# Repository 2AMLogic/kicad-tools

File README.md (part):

# kicad-tools

**Tools for AI agents to work with KiCad projects.**

🌐 **Live demo gallery: [kicad-tools.org](https://kicad-tools.org)** — explore example boards built end-to-end by these tools, with 2D/3D renders, routing & manufacturing metrics, downloadable fabrication packages, and an interactive in-browser PCB viewer.

This project provides standalone Python tools that enable AI agents (LLMs, autonomous coding assistants, etc.) to parse, analyze, and manipulate KiCad schematic and PCB files programmatically. All tools output machine-readable JSON and require no running KiCad instance.

**Preparing a board for JLCPCB assembly?** Check the layout against JLCPCB rules, look up LCSC parts, and export Gerbers, a bill of materials and component placements. With a signed-off bundle, `kct submit-jlcpcb --dry-run` checks stock for your board quantity and writes a local submission plan and review page. [JLCPCB assembly walkthrough](docs/guides/submission-preparation.md)

## Why Agent-Focused?

Traditional EDA tools require GUIs and manual interaction. `kicad-tools` bridges the gap by providing:

- **Structured data access** - Parse KiCad files into clean Python objects
- **Machine-readable output** - Analysis and query commands offer JSON output; check each command’s `--help` for supported formats
- **Programmatic modification** - Edit schematics and PCBs without a GUI
- **LLM reasoning interface** - Purpose-built module for LLM-driven PCB layout decisions

Whether you're building an AI assistant that reviews PCB designs, automating DRC checks in CI, or experimenting with LLM-driven routing, these tools provide the foundation.

## Installation

```bash
# Base install (CPU only)
pip install kicad-tools

# With CUDA GPU acceleration (NVIDIA GPUs on Linux/Windows)
pip install kicad-tools[cuda]

# With Metal GPU acceleration (Apple Silicon Macs)
pip install kicad-tools[metal]

# With native C++ router backend
pip install kicad-tools[native]

# With CMA-ES placement optimization (kct optimize-placement / kct build --optimize-placement)
pip install kicad-tools[placement]

# Everything (all optional dependencies)
pip install kicad-tools[all]
```

> The `placement` extra pulls in `cmaes` (and, transitively, `scipy`). It is
> required by `kct optimize-placement` and the placement step of
> `kct build --optimize-placement`; without it those commands exit with a
> clear message naming the extra. The `dev` and `all` extras already include
> it, so `uv sync --extra dev` is sufficient for development.

To check GPU acceleration status:
```bash
kct calibrate --show-gpu
```

### In a board (consumer) repository

The supported setup for a PCB-design repo that depends on kicad-tools is **PyPI
plus a committed `uv.lock`**: `pyproject.toml` carries a lower bound
(`kicad-tools[<extras>]>=X`) and `uv.lock` is the exact pin. Install it, with
the agent skills, CI gates and conventions, from a kicad-tools checkout:

```bash
./scripts/install-kct.sh /path/to/board-repo        # PyPI floor (default; same as --pypi)
./scripts/install-kct.sh --upgrade-workflow /path/to/board-repo  # + weekly upgrade PR
cd /path/to/board-repo && uv lock && uv sync && uv run kct build-native
```

The installer keeps the repo's existing extras and removes any
`[tool.uv.sources]` kicad-tools entry. Re-running it is a no-op when the floor
is already current. `--upgrade-workflow` adds `.github/workflows/kct-upgrade.yml`,
which opens a PR for each new PyPI release; the PR raises the floor, refreshes
`uv.lock` and the vendored files, and lists the release's upgrade notes.
`kct doctor` checks that the vendored files match the installed version.

Git and SHA pins (`--tag vX.Y.Z`, `--rev <sha>`) and local checkouts
(`--path ../kicad-tools`) are escape hatches for short-lived use. If you need
a fix that is not on PyPI yet, ask for a patch release rather than carrying a
SHA pin. Run `./scripts/install-kct.sh --help` for every option.

## Quick Start

### Command Line (`kct`)

```bash
# List symbols in a schematic
kct symbols project.kicad_sch
kct symbols project.kicad_sch --format json

# Trace nets
kct nets project.kicad_sch
kct nets project.kicad_sch --net VCC

# Generate bill of materials
kct bom project.kicad_sch
kct bom project.kicad_sch --format csv --group

# Run ERC (requires kicad-cli)
kct erc project.kicad_sch
kct erc project.kicad_sch --errors-only

# Run DRC with manufacturer rules
kct drc board.kicad_pcb
kct drc board.kicad_pcb --mfr jlcpcb
kct mfr compare  # Compare manufacturer rules
```

### Python API

```python
from kicad_tools import load_schematic, Schematic

# Load and parse a schematic
doc = load_schematic("project.kicad_sch")
sch = Schematic(doc)

# Access symbols
for symbol in sch.symbols:
    print(f"{symbol.reference}: {symbol.value}")

# Access hierarchy
for sheet in sch.sheets:
    print(f"Sheet: {sheet.name}")
```

### PCB Autorouter

```python
from kicad_tools.router import Autorouter, DesignRules

# Configure design rules
rules = DesignRules(
    grid_resolution=0.25,  # mm
    trace_width=0.2,  # mm
    trace_clearance=0.15,  # mm
)

# Create router and add components
router = Autorouter(width=100, height=80, rules=rules)
router.add_component("U1", pads=[{"number": "1", "x": 10, "y": 10, "net": 1}])
router.add_component("U2", pads=[{"number": "1", "x": 20, "y": 10, "net": 1}])

# Route all nets
routes = router.route_all(timeout=30)
print(f"Created {len(routes)} routes")
```

### LLM-Driven PCB Layout

The reasoning module enables LLMs to make strategic PCB layout decisions while tools handle geometric execution:

```python
from kicad_tools import PCBReasoningAgent

# Load board
agent = PCBReasoningAgent.from_pcb("board.kicad_pcb")

# Reasoning loop
while not agent.is_complete():
    # Get state as prompt for LLM
    prompt = agent.get_prompt()

    # Call your LLM (OpenAI, Anthropic, local, etc.)
    command = call_llm(prompt)

    # Execute and get feedback
    result, diagnosis = agent.execute(command)

# Save result
agent.save("board_routed.kicad_pcb")
```

CLI usage:
```bash
# Export state for external LLM
kct reason board.kicad_pcb --export-state

# Interactive mode
kct reason board.kicad_pcb --interactive

# Auto-route priority nets
kct reason board.kicad_pcb --auto-route
```

See `examples/llm-routing/` for complete examples.

### MCP Server for AI Agents

Enable AI assistants like Claude to interact with KiCad designs via the Model Context Protocol:

```bash
# Install with MCP support
pip install "kicad-tools[mcp]"

# Run the MCP server
kct mcp serve
```

Register the server with your agent harness. `kct mcp setup` finds the
absolute `kct` path, merges into the existing config without touching other
servers, and is a no-op when re-run (`--dry-run` previews, `--format json` for
scripts):

```bash
kct mcp setup --client claude-code      # ~/.claude.json via `claude mcp add-json` (default; --scope project for ./.mcp.json)
kct mcp setup --client claude-desktop   # Claude Desktop config
kct mcp setup --client codex            # [mcp_servers.kct] in $CODEX_HOME/config.toml
kct mcp setup --client opencode         # ~/.config/opencode/opencode.json (--project for ./opencode.json)
```

Or configure Claude Desktop by hand (`~/Library/Application Support/Claude/claude_desktop_config.json`):

```json
{
  "mcpServers": {
    "kicad-tools": {
      "command": "python",
      "args": ["-m", "kicad_tools.mcp.server"]
    }
  }
}
```

Available MCP tools:
- **Analysis**: `board_summary`, `get_drc_violations`, `measure_clearance`
- **Export**: `export_gerbers`, `export_bom`, `export_assembly`
- **Placement**: `placement_analyze`, `placement_suggestions`
- **Sessions**: `start_session`, `query_move`, `apply_move`, `commit`, `rollback`
- **Routing**: `route_net`, `route_net_auto`, `get_unrouted_nets`
- **Optimization**: `optimize_placement`, `evaluate_placement`

See `docs/mcp/` for complete documentation.

### Circuit Blocks

Build schematics using reusable, tested circuit blocks:

```python
from kicad_tools.schematic.models import Schematic
from kicad_tools.schematic.blocks import (
    MCUBlock,
    CrystalOscillator,
    LDOBlock,
    USBConnector,
    DebugHeader,
    I2CPullups,
    ResetButton,
)

sch = Schematic("My STM32 Design")

# Add an MCU with bypass capacitors
mcu = MCUBlock(
    sch, x=150, y=100, part="STM32F103C8T6", bypass_caps=["100nF", "100nF", "100nF", "4.7uF"]
)

# Add crystal oscillator
xtal = CrystalOscillator(sch, x=100, y=100, frequency="8MHz", load_caps="20pF")

# Add power supply
ldo = LDOBlock(sch, x=50, y=100, input_voltage=5.0, output_voltage=3.3)

# Add USB connector with ESD protection
usb = USBConnector(sch, x=50, y=150, connector_type="type-c", esd_protection=True)

# Add debug header for programming
debug = DebugHeader(sch, x=200, y=100, interface="swd")

# Add I2C pull-ups
i2c = I2CPullups(sch, x=180, y=150, pullup_value="4.7k")

# Add reset button with debounce
reset = ResetButton(sch, x=120, y=50, debounce_cap="100nF")

# Connect via ports
sch.add_wire(ldo.port("VOUT"), mcu.port("VDD"))
sch.add_wire(xtal.port("OUT"), mcu.port("OSC_IN"))

sch.save()
```

Available blocks:
- **MCUBlock**: Microcontroller with bypass capacitors
- **CrystalOscillator**: Crystal/oscillator with load capacitors
- **LDOBlock**: Linear regulator with input/output capacitors
- **USBConnector**: USB-B/Mini/Micro/Type-C with optional ESD protection
- **DebugHeader**: SWD/JTAG/Tag-Connect programming headers
- **I2CPullups**: I2C bus pull-up resistors with optional filtering
- **ResetButton**: Reset switch with debounce capacitor
- **BarrelJackInput/USBPowerInput/BatteryInput**: Power input circuits
- **LEDIndicator**: Status LED with current-limiting resistor
- **DecouplingCaps**: Decoupling capacitor placement

See `boards/04-stm32-devboard/` for a complete design example.

### Project Workflow

Work with complete KiCad projects using the unified Project class:

```python
from kicad_tools import Project

# Load a KiCad project
project = Project.load("myboard.kicad_pro")

# Cross-reference schematic to PCB
result = project.cross_reference()
print(f"Unplaced components: {result.unplaced}")

# Export manufacturing files
project.export_assembly("output/", manufacturer="jlcpcb")
```

### Progress Callbacks

Monitor long-running operations with progress callbacks:

```python
from kicad_tools import ProgressCallback, ProgressContext
from kicad_tools.router import Autorouter

def on_progress(progress: float, message: str, cancelable: bool) -> bool:
    print(f"{progress * 100:.0f}%: {message}")
    return True  # Return False to cancel

# Use with context manager
with ProgressContext(on_progress):
    router = Autorouter(...)
    router.route_all()  # Progress reported automatically

# Or create JSON-formatted callbacks for automation
from kicad_tools import create_json_callback

callback = create_json_callback()
```

### Parametric Footprint Generators

Create KiCad footprints programmatically with IPC-7351 naming:

```python
from kicad_tools.library import create_soic, create_qfp, create_chip

# Generate SOIC-8 footprint
fp = create_soic(pins=8, pitch=1.27)
fp.save("SOIC-8.kicad_mod")

# Generate LQFP-48
fp = create_qfp(pins=48, pitch=0.5, body_size=7.0)
fp.save("LQFP-48.kicad_mod")

# Generate 0402 chip resistor
fp = create_chip("0402", prefix="R")
fp.save("R_0402.kicad_mod")
```

Available generators: `create_soic`, `create_qfp`, `create_qfn`, `create_sot`, `create_chip`, `create_dip`, `create_pin_header`.

### Symbol Library Management

Create and edit KiCad symbol libraries programmatically:

```python
from kicad_tools.schema.library import SymbolLibrary

# Create a new symbol library
lib = SymbolLibrary.create("myproject.kicad_sym")

# Create a symbol with pins
sym = lib.create_symbol("MyPart")
sym.add_pin("1", "VCC", "power_in", (0, 5.08))
sym.add_pin("2", "GND", "power_in", (0, -5.08))
sym.add_pin("3", "IN", "input", (-7.62, 0))
sym.add_pin("4", "OUT", "output", (7.62, 0))

# Save the library
lib.save()

# Load and edit existing library
lib = SymbolLibrary.load("existing.kicad_sym")
```

### Pure Python DRC

Run design rule checks without requiring kicad-cli:

```bash
# Check against manufacturer rules
kct check board.kicad_pcb --mfr jlcpcb --format json

# Check against a 4-layer rule set with 2 oz outer / 0.5 oz inner copper.
# (A scalar `--copper 2` would also apply 2 oz to inner layers; omit the flag
# when the board declares a stackup.)
kct check board.kicad_pcb --mfr jlcpcb --layers 4 --copper outer=2,inner=0.5
```

Python API:

```python
from kicad_tools.schema.pcb import PCB
from kicad_tools.validate import DRCChecker

pcb = PCB.load("board.kicad_pcb")
checker = DRCChecker(pcb, manufacturer="jlcpcb")
results = checker.check_all()

print(results.summary())
for violation in results:
    print(f"  {violation.rule_id}: {violation.message}")
```

### Placement Optimization

Optimize component placement using physics-based or evolutionary algorithms:

```python
from kicad_tools.optim import PlacementOptimizer, EvolutionaryPlacementOptimizer
from kicad_tools.schema.pcb import PCB

pcb = PCB.load("board.kicad_pcb")

# Physics-based optimization (force-directed)
optimizer = PlacementOptimizer.from_pcb(pcb)
optimizer.run(iterations=1000, dt=0.01)

# Get optimized placements
for comp in optimizer.components:
    print(f"{comp.ref}: ({comp.x:.2f}, {comp.y:.2f}) @ {comp.rotation:.1f}°")

# Evolutionary optimization (genetic algorithm)
evo = EvolutionaryPlacementOptimizer.from_pcb(pcb)
best = evo.optimize(generations=100, population_size=50)

# Hybrid: evolutionary global search + physics refinement
physics_opt = evo.optimize_hybrid(generations=50)
physics_opt.write_to_pcb(pcb)
pcb.save("optimized.kicad_pcb")
```

CLI usage:
```bash
kct placement optimize board.kicad_pcb --iterations 1000
```

### Trace Optimization

Optimize routed traces for shorter paths and fewer vias:

```python
from kicad_tools.router import TraceOptimizer
from kicad_tools.schema.pcb import PCB

pcb = PCB.load("board.kicad_pcb")
optimizer = TraceOptimizer(pcb)
optimizer.optimize()
pcb.save("optimized.kicad_pcb")
```

CLI usage:
```bash
kct optimize-traces board.kicad_pcb -o optimized.kicad_pcb
```

### Datasheet Tools

Search, download, and parse component datasheets:

```bash
# Search for datasheets
kct datasheet search STM32F103C8T6

# Download a datasheet
kct datasheet download STM32F103C8T6 -o datasheets/

# Convert PDF to markdown
kct datasheet convert datasheet.pdf -o datasheet.md

# Extract images and tables
kct datasheet extract-images datasheet.pdf -o images/
kct datasheet extract-tables datasheet.pdf
```

Python API:

```python
from kicad_tools.datasheet import DatasheetManager, DatasheetParser

# Search and download
manager = DatasheetManager()
results = manager.search("STM32F103C8T6")
datasheet = manager.download(results[0])

# Parse PDF
parser = DatasheetParser("STM32F103.pdf")
markdown = parser.to_markdown()

# Extract images and tables
images = parser.extract_images()
tables = parser.extract_tables()
for table in tables:
    print(table.to_markdown())
```

### Parts Lookup (LCSC / JLCPCB)

Look up LCSC part numbers, check BOM availability, and pull pricing/stock:

```python
from kicad_tools.parts import LCSCClient

client = LCSCClient()
part = client.lookup("C2040")
if part:
    print(f"{part.mfr_part}: {part.stock} in stock, best ${part.best_price:.4f}")
```

Part lookups resolve through a tiered chain (each tier falls back to the next):

1. **Local response cache** — previously fetched parts.
2. **Official JLCPCB open-platform API** — only when you supply your own API key
   (see below). Off by default; inert without keys.
3. **Anonymous scrape API** — the public JLCPCB web endpoints (requires the
   `parts` extra: `pip install "kicad-tools[parts]"`). **Note:** as of
   July 2026 JLCPCB's public endpoint returns 404 — treat this tier as
   best-effort/deprecated and rely on tier 2 (BYO key) or tier 4 (offline).
4. **Offline jlcparts catalog** — a locally synced mirror
   (`kct parts sync-catalog`, ~620 MB download, ~5 GB on disk, ~7.1 M
   components), usable fully offline.

#### Using your own JLCPCB API key

kicad-tools can talk to the **official JLCPCB open-platform API** using
credentials you register yourself at the JLCPCB developer portal
(<https://jlcpcb.com/> → developer/open platform). This is strictly opt-in: you
bring your own key, kicad-tools ships only the signed client. **Without keys,
behavior is unchanged** — the official tier is simply skipped.

Set all three environment variables (kicad-tools reads them via `os.environ`;
it does **not** load a `.env` file itself, so use your shell, `direnv`, or a
dotenv runner — see [`.env.example`](.env.example)):

```bash
export JLCPCB_APP_ID="your-app-id"
export JLCPCB_ACCESS_KEY="your-access-key"
export JLCPCB_SECRET_KEY="your-secret-key"
```

All three must be set (and non-empty) to activate the official tier; if any is
missing it stays inert. Once set, `LCSCClient.lookup()` / `lookup_many()` prefer
the official API for part-detail-by-code, falling back down the chain above on
any failure.

Notes and caveats:

- **What it unlocks:** authenticated *part detail lookup by LCSC code* only.
  There is **no confirmed official keyword/MPN search endpoint**, so
  `LCSCClient.search()` always uses the anonymous/offline path even with keys.
- **IP whitelisting:** the developer portal offers an IP-whitelist feature. If
  you enable it, your machine's public IP must be whitelisted or requests are
  rejected (surfaced as a distinct, actionable error).
- **Never commit credentials.** `.env` is gitignored; the secret key is used
  only as HMAC key material and is never transmitted.
- The request-signing scheme is not first-party-documented by JLCPCB; the client
  implements the best-available community-reverse-engineered variant for the
  Parts surface, with the two ambiguous parameters isolated as single
  flip-points in `parts/jlcpcb_api.py` (see that module and issue #4118).

## CLI Commands

### Unified CLI (`kct` or `kicad-tools`)

The commands below are the ones most workflows reach for. The authoritative
full list (every command and subcommand) lives in
[CLI Reference → Commands Overview](docs/reference/cli.md#commands-overview).

**Inspection and validation**

| Command | Description |
|---------|-------------|
| `kct symbols <schematic>` | List symbols with filtering |
| `kct nets <schematic>` | Trace and analyze nets |
| `kct bom <schematic>` | Generate bill of materials |
| `kct erc <schematic>` | Run electrical rules check |
| `kct drc <pcb>` | Run design rules check (requires kicad-cli) |
| `kct check <pcb>` | Pure Python DRC (no kicad-cli needed) |
| `kct creepage <pcb>` | HV surface-path (creepage) audit vs IEC 60664-1 / 62368-1 |
| `kct creepage-export-rules <project>` | Export voltage-domain netclasses + pairwise HV clearance rules so kicad-cli DRC enforces creepage |
| `kct analyze <pcb>` | Signal-integrity, current-sense, electrical-rating, and operating-state component-stress lint |
| `kct audit <project>` | Manufacturing readiness audit (ERC, DRC, connectivity, compatibility) |
| `kct impedance <subcommand>` | Transmission line impedance calculations |

**Layout and routing**

| Command | Description |
|---------|-------------|
| `kct route <pcb>` | Autoroute a PCB (`--nets`/`--skip-nets` to select nets, `--complete` to finish one) |
| `kct route-auto <pcb>` | Orchestrator-based multi-strategy autorouting |
| `kct optimize-traces <pcb>` | Optimize routed traces |
| `kct placement <pcb>` | Detect and optimize component placement |
| `kct optimize-placement <pcb>` | CMA-ES/Bayesian (`--strategy bayesian`, needs `kicad-tools[bayesian]`) global placement optimization |
| `kct zones <subcommand>` | Add copper pour zones (and `hv-keepout` plane voids) |
| `kct stitch <pcb>` | Auto-add stitching vias for plane connections |
| `kct reason <pcb>` | LLM-driven PCB layout reasoning |

**Repair**

| Command | Description |
|---------|-------------|
| `kct fix-drc <pcb>` | Automated DRC violation repair (clearance + drill + mask-copper) |
| `kct fix-erc <schematic>` | Automated ERC violation repair (PWR_FLAG + no-connect) |
| `kct fix-vias <pcb>` | Fix vias to meet manufacturer specifications (incl. off-pad relocation) |
| `kct pipeline <input>` | End-to-end repair pipeline for existing PCBs |

**Parts and manufacturing**

| Command | Description |
|---------|-------------|
| `kct datasheet <subcommand>` | Search, download, parse datasheets |
| `kct parts <subcommand>` | LCSC/JLCPCB part lookup, cache, offline catalog sync |
| `kct export <pcb>` | Manufacturing bundle export (gerbers, BOM, CPL) |
| `kct submit-jlcpcb <bundle>` | Prepare a signed-off JLCPCB assembly bundle for review. See the [dry-run example](docs/guides/submission-preparation.md). |
| `kct export-formats <pcb>` | PDF / SVG / STEP / IPC-2581 / ODB++ via kicad-cli, with a per-format result |
| `kct mfr <subcommand>` | Manufacturer rule profiles (apply-rules, validate) |
| `kct spec <subcommand>` | Project specification (`.kct`) management |
| `kct fleet status` | Routing + manufacturing readiness across all boards |

**Environment**

| Command | Description |
|---------|-------------|
| `kct doctor` | Diagnose kicad-tools installation health (version-record drift) |
| `kct build-native` | Build the C++ router backend for 10-100x faster routing |
| `kct mcp serve` | Start MCP server for AI agent integration |

Every `kct` subcommand that produces a result accepts `--format json` for
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
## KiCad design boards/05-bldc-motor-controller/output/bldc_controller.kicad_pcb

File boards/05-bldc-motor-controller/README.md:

# Sensored BLDC Controller

Revision B is a real 42-component, 70 × 90 mm, four-layer small-motor controller:
ATmega328P-AU, DRV8313PWPR integrated triple half bridge, and TPS7A1650DGNR
5 V supply. It includes reverse-input protection, fuse, transient clamp,
charge-pump capacitors, current comparator, Hall inputs, AVR ISP, RUN switch
input, speed trimmer and working commutation firmware.

Start at 12 V with a 0.5 A current-limited bench supply, an unloaded motor,
RUN open and the speed input at its measured low-voltage end. The initial
phase-current target is 0.5 A; the nominal comparator trip is 1 A and firmware
caps duty at 25%. Physical motor operation and thermal performance have not
yet been measured. Read [HARDWARE.md](redesign/HARDWARE.md) before assembly,
programming or power-up; it contains all connector pinouts and verified BOM identities.

Assembly export checks stock for all 22 LCSC numbers. On a fresh machine,
`uv run kct parts sync-catalog` downloads the parts catalog. If preflight
reports a missing part, look up its LCSC number. For example,
`uv run kct parts lookup --no-cache C3167176` refreshes the stock record for fuse F1.

Generate the circuit and reviewed route, run native and manufacturer checks,
and export the assembly bundle with the board recipe.

```sh
uv run python boards/05-bldc-motor-controller/design.py [output-directory]
```

Failed reconstruction leaves the preceding output intact. The route is explicit
reviewed copper in `redesign/routing.json`, guarded by a hash of the actual
component/pad/placement/net geometry. It combines automatic routing with manual
physical corrections; changing circuit geometry requires a new route and fresh
gates. No synthetic routing pads are present in the generated board.

The active revision-B recipe calls the generic physical power-stitch transaction
before its final native and manufacturing gates. It accepts existing complete
power copper or a safely completed candidate after real refill, preserving all
previous pad bonds and rejecting new native findings. Its retained `readiness/stitch`
ledger contains saved, refilled-before, proposed and refilled-candidate bytes,
native reports and physical pad components. Failed stage evidence is retained in
the `bldc-power-stitch-*` temporary directory named by the error.

Fresh reconstruction at main `7368bf597eaefb2dbe171f79db3c3216843a2ae6` already had
zero native opens/errors and clean copper LVS (149 bound pads); the historical
57-open legacy audit does not describe this active recipe. The generic split-plane
regression in `tests/fixtures/stitch-5388` demonstrates why added vias alone cannot
prove completion. Issue #4410 remains open for its later routing/Kelvin/QFN phases.

The JLCPCB placement file lists all 42 assembly parts, including 36 SMT parts
and the six through-hole parts J1–J5 and RV1. The three board fiducials appear
in the fabrication artwork and are excluded from the placement file.
Solder both driver/regulator exposed pads. Use the included local symbol and
footprint libraries, native drawings, BOM/CPL and firmware. Fresh reconstruction
passed native KiCad DRC/ERC with zero findings and manufacturer checks with
zero errors or warnings. These fabrication checks do not replace motor and
thermal bench validation.

The original DRV8301 circuit is retained in [legacy_drv8301](legacy_drv8301/ARCHIVE.md)
as an electrically invalid historical regression fixture, documented in
[issue #4993](https://github.com/rjwalters/kicad-tools/issues/4993). Its generator
writes `regression-output`; the default command above builds revision B.

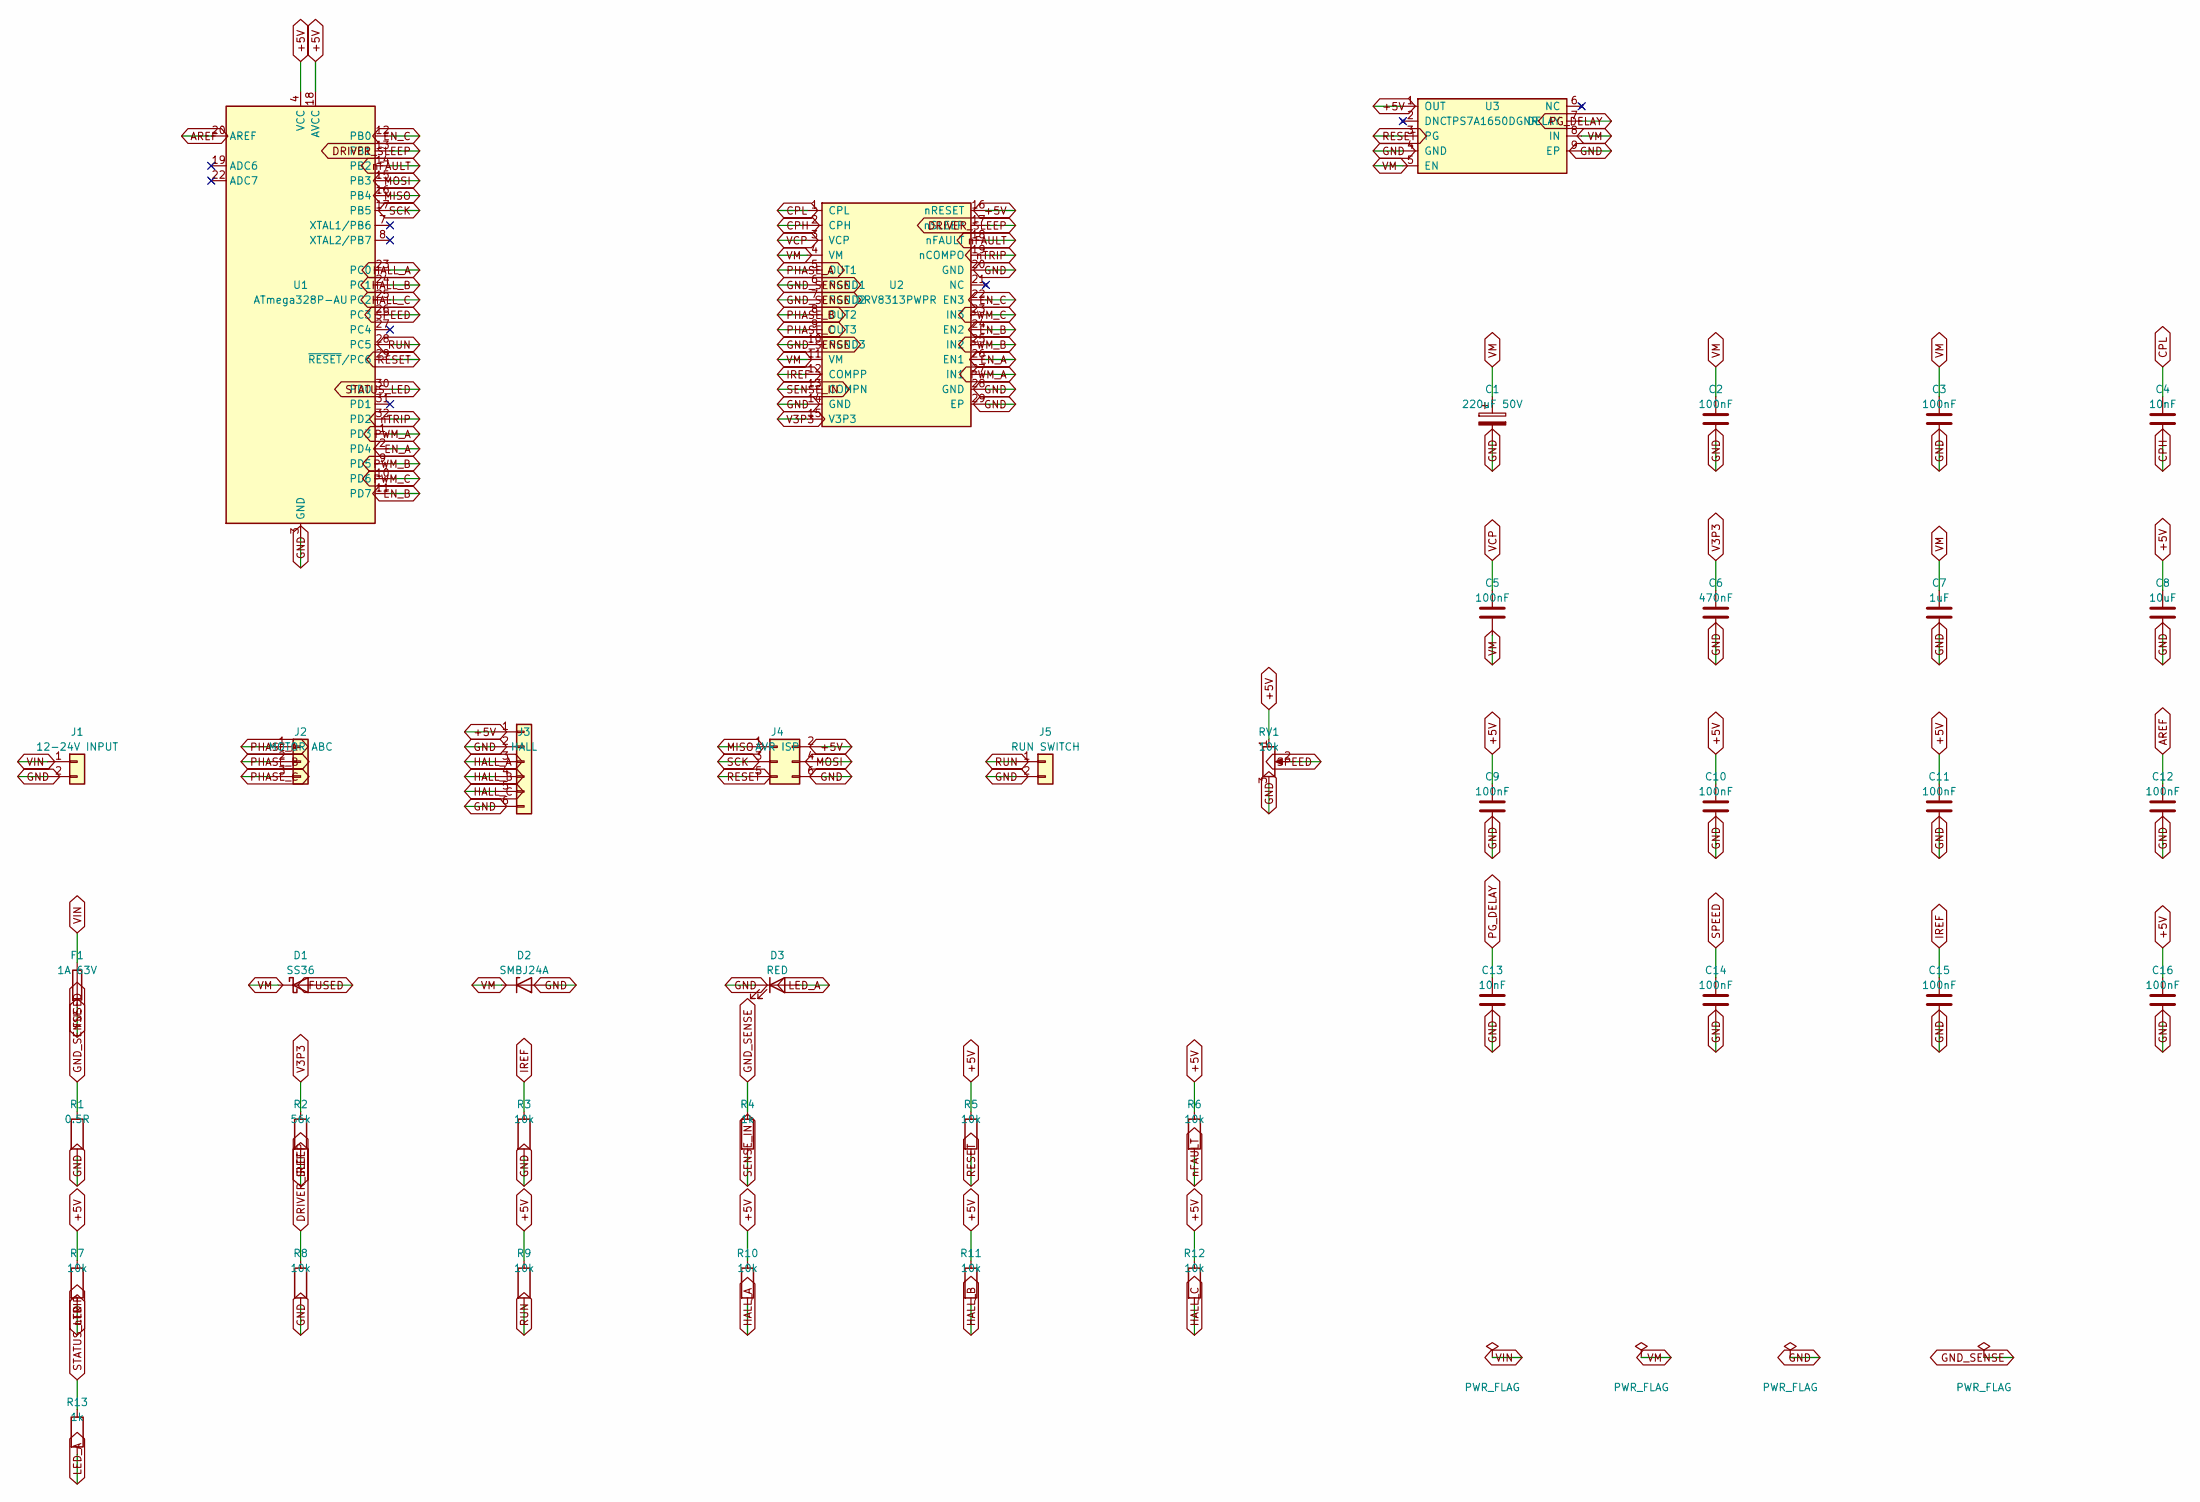
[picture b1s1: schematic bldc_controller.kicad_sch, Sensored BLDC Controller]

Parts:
C1: 220uF 50V; CP_Elec_8x10.5_PolarityMark; MPN EEEFT1H221AP; LCSC C178594
C2, C3, C5, C9, C10, C11, C12, C14, C15, C16: 100nF; C_0805_2012Metric; MPN CC0805KRX7R9BB104; LCSC C49678
C4, C13: 10nF; C_0805_2012Metric; MPN CL21B103KBANNNC; LCSC C1710
C6: 470nF; C_0805_2012Metric; MPN CL21B474KBFNNNE; LCSC C13967
C7: 1uF; C_0805_2012Metric; MPN CL21B105KBFNNNE; LCSC C28323
C8: 10uF; C_0805_2012Metric; MPN CL21A106KAYNNNE; LCSC C15850
D1: SS36; D_SMA; MPN SS36; LCSC C16015
D2: SMBJ24A; D_SMB; MPN SMBJ24A; LCSC C224017
D3: RED; LED_0805_2012Metric; MPN NCD0805R1; LCSC C84256
F1: 1A 63V; Fuse_1206_3216Metric; MPN SF-1206S100-2; LCSC C3167176
J1: 12-24V INPUT; PinHeader_1x02_P2.54mm_Vertical; MPN ZX-PZ2.54-1-2PZZ; LCSC C7501260
J2: MOTOR ABC; PinHeader_1x03_P2.54mm_Vertical; MPN 2.54-1*3P; LCSC C49257
J3: HALL; PinHeader_1x06_P2.54mm_Vertical; MPN 2.54-1*6P; LCSC C37208
J4: AVR ISP; PinHeader_2x03_P2.54mm_Vertical; MPN 2.54-2*3P; LCSC C65114
J5: RUN SWITCH; PinHeader_1x02_P2.54mm_Vertical; MPN ZX-PZ2.54-1-2PZZ; LCSC C7501260
R1: 0.5R; R_2512_6332Metric; MPN WSL2512R5000FEA; LCSC C511023
R2: 56k; R_0805_2012Metric; MPN 0805W8F5602T5E; LCSC C17756
R3, R5, R6, R7, R8, R9, R10, R11, R12: 10k; R_0805_2012Metric; MPN 0805W8F1002T5E; LCSC C17414
R4, R13: 1k; R_0805_2012Metric; MPN 0805W8F1001T5E; LCSC C17513
RV1: 10k; Potentiometer_Bourns_3296W_Vertical; MPN 3296W-1-103LF; LCSC C34846
U1: ATmega328P-AU; TQFP-32_7x7mm_P0.8mm; MPN ATMEGA328P-AU; LCSC C14877
U2: DRV8313PWPR; TI_PWP0028C_EP3.4x9.7_Mask3.1x5.18_ThermalVias; MPN DRV8313PWPR; LCSC C92482
U3: TPS7A1650DGNR; TI_DGN0008C_Lands1.4x0.45_EP1.57x1.89_ThermalVias; MPN TPS7A1650DGNR; LCSC C468238

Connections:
+5V: C8.1, C9.1, C10.1, C11.1, C16.1, J3.1, J4.2, R5.1, R6.1, R7.1, R9.1, R10.1, R11.1, R12.1, RV1.1, U1.4 (VCC), U1.6 (VCC), U1.18 (AVCC), U2.16 (nRESET), U3.1 (OUT)
AREF: C12.1, U1.20 (AREF)
CPH: C4.2, U2.2 (CPH)
CPL: C4.1, U2.1 (CPL)
DRIVER_SLEEP: R8.1, U1.13 (PB1), U2.17 (nSLEEP)
EN_A: U1.2 (PD4), U2.26 (EN1)
EN_B: U1.11 (PD7), U2.24 (EN2)
EN_C: U1.12 (PB0), U2.22 (EN3)
FUSED: D1.2 (A), F1.2
HALL_A: J3.3, R10.2, U1.23 (PC0)
HALL_B: J3.4, R11.2, U1.24 (PC1)
HALL_C: J3.5, R12.2, U1.25 (PC2)
IREF: C15.1, R2.2, R3.1, U2.12 (COMPP)
LED_A: D3.2 (A), R13.2
MISO: J4.1, U1.16 (PB4)
MOSI: J4.4, U1.15 (PB3)
PG_DELAY: C13.1, U3.7 (DELAY)
PHASE_A: J2.1, U2.5 (OUT1)
PHASE_B: J2.2, U2.8 (OUT2)
PHASE_C: J2.3, U2.9 (OUT3)
PWM_A: U1.1 (PD3), U2.27 (IN1)
PWM_B: U1.9 (PD5), U2.25 (IN2)
PWM_C: U1.10 (PD6), U2.23 (IN3)
RESET: J4.5, R5.2, U1.29 (~RESET/PC6), U3.3 (PG)
RUN: J5.1, R9.2, U1.28 (PC5)
SCK: J4.3, U1.17 (PB5)
SENSE_IN: R4.2, U2.13 (COMPN)
SPEED: C14.1, RV1.2, U1.26 (PC3)
STATUS_LED: R13.1, U1.30 (PD0)
V3P3: C6.1, R2.1, U2.15 (V3P3)
VCP: C5.1, U2.3 (VCP)
nFAULT: R6.2, U1.14 (PB2), U2.18 (nFAULT)
nTRIP: R7.2, U1.32 (PD2), U2.19 (nCOMPO)

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
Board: 4 copper layers, 42 parts (0 on the bottom side), 37 nets, no tracks yet.

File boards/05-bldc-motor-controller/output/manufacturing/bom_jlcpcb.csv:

Comment,Designator,Footprint,LCSC Part #
0.5R,R1,Resistor_SMD:R_2512_6332Metric,C511023
100nF,"C10,C11,C12,C14,C15,C16,C2,C3,C5,C9",Capacitor_SMD:C_0805_2012Metric,C49678
10k,RV1,Potentiometer_THT:Potentiometer_Bourns_3296W_Vertical,C34846
10k,"R10,R11,R12,R3,R5,R6,R7,R8,R9",Resistor_SMD:R_0805_2012Metric,C17414
10nF,"C13,C4",Capacitor_SMD:C_0805_2012Metric,C1710
10uF,C8,Capacitor_SMD:C_0805_2012Metric,C15850
12-24V INPUT; RUN SWITCH,"J1,J5",Connector_PinHeader_2.54mm:PinHeader_1x02_P2.54mm_Vertical,C7501260
1A 63V,F1,Fuse:Fuse_1206_3216Metric,C3167176
1k,"R13,R4",Resistor_SMD:R_0805_2012Metric,C17513
1uF,C7,Capacitor_SMD:C_0805_2012Metric,C28323
220uF 50V,C1,board05_revB:CP_Elec_8x10.5_PolarityMark,C178594
470nF,C6,Capacitor_SMD:C_0805_2012Metric,C13967
56k,R2,Resistor_SMD:R_0805_2012Metric,C17756
ATmega328P-AU,U1,Package_QFP:TQFP-32_7x7mm_P0.8mm,C14877
AVR ISP,J4,Connector_PinHeader_2.54mm:PinHeader_2x03_P2.54mm_Vertical,C65114
DRV8313PWPR,U2,board05_revB:TI_PWP0028C_EP3.4x9.7_Mask3.1x5.18_ThermalVias,C92482
HALL,J3,Connector_PinHeader_2.54mm:PinHeader_1x06_P2.54mm_Vertical,C37208
MOTOR ABC,J2,Connector_PinHeader_2.54mm:PinHeader_1x03_P2.54mm_Vertical,C49257
RED,D3,LED_SMD:LED_0805_2012Metric,C84256
SMBJ24A,D2,Diode_SMD:D_SMB,C224017
SS36,D1,Diode_SMD:D_SMA,C16015
TPS7A1650DGNR,U3,board05_revB:TI_DGN0008C_Lands1.4x0.45_EP1.57x1.89_ThermalVias,C468238

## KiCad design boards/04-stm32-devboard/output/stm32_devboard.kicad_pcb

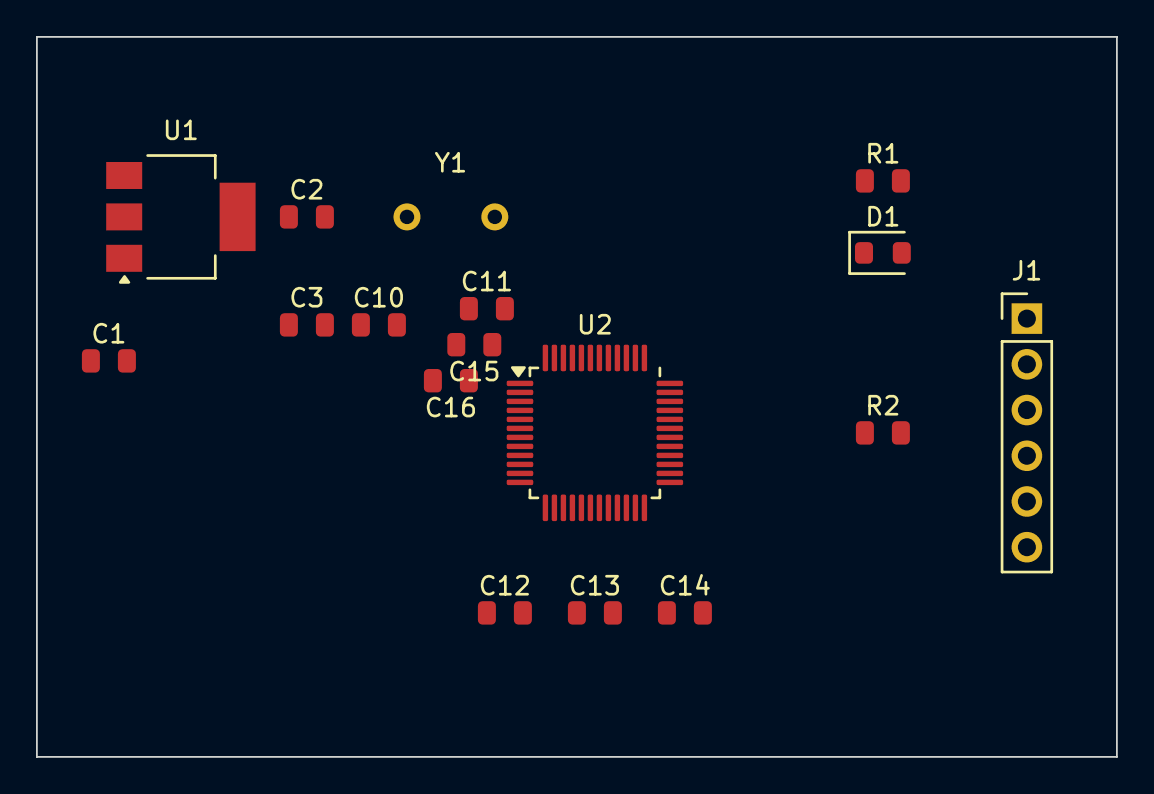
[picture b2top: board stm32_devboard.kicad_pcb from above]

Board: 2 copper layers, 60.0 x 40.0 mm, 17 parts (0 on the bottom side), 12 nets, no tracks yet.

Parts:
C1, C2: 10uF; C_0805_2012Metric
C3, C12, C13, C14, C15: 100nF; C_0805_2012Metric
C10, C11: 20pF; C_0805_2012Metric
C16: 4.7uF; C_0805_2012Metric
D1: LED; LED_0805_2012Metric
J1: SWD-6; PinHeader_1x06_P2.54mm_Vertical
R1: 330R; R_0805_2012Metric
R2: 10k; R_0805_2012Metric
U1: MCP1825S-3302E/DB; SOT-223-3_TabPin2
U2: STM32F103C8T6; LQFP-48_7x7mm_P0.5mm
Y1: 8MHz; Crystal_HC49-4H_Vertical

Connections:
+3.3V: C2.1, C3.1, C12.1, C13.1, C14.1, C15.1, C16.1, J1.1, R1.1, U1.3 (VO), U2.1 (VBAT), U2.9 (VDDA), U2.24 (VDD), U2.36 (VDD), U2.48 (VDD)
+5V: C1.1, U1.1 (VI)
BOOT0: R2.1, U2.44 (BOOT0)
GND: C1.2, C2.2, C3.2, C10.2, C11.2, C12.2, C13.2, C14.2, C15.2, C16.2, J1.6, R2.2, U1.2 (GND), U2.8 (VSSA), U2.23 (VSS), U2.35 (VSS), U2.47 (VSS)
LED_K: D1.1 (K), R1.2
NRST: J1.5, U2.7 (NRST)
OSC_IN: C10.1, U2.5 (PD0), Y1.1
OSC_OUT: C11.1, U2.6 (PD1), Y1.2
SWCLK: J1.3, U2.37 (PA14)
SWDIO: J1.2, U2.34 (PA13)
SWO: J1.4, U2.39 (PB3)
USER_LED: D1.2 (A), U2.25 (PB12)

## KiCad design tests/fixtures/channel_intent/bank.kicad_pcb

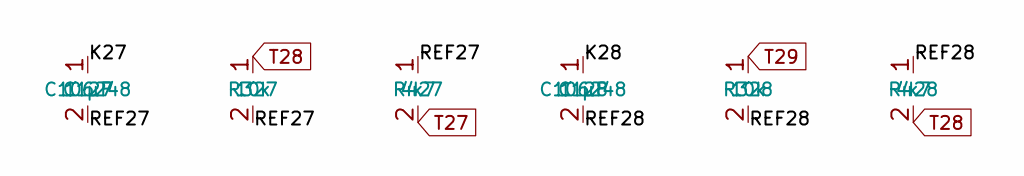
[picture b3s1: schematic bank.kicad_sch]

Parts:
C127, C128: 1 µF; LCSC C106248
R327, R328: 10k
R427, R428: 4k7

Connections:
/K27: C127.1
/K28: C128.1
/REF27: C127.2, R327.2, R427.1
/REF28: C128.2, R328.2, R428.1
T27: R427.2
T28: R327.1, R428.2
T29: R328.1

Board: 2 copper layers, 6 parts (0 on the bottom side), 3 nets, no tracks yet.

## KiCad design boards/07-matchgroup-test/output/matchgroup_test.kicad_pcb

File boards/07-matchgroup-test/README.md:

# 07 — 8 MiB SDRAM exerciser

A standalone STM32F429ZIT6 MCU tests an IS42S16400J-6TLI-TR x16 SDR SDRAM.
The real circuit replaces the former synthetic DDR/MIPI/HDMI routing fixture.
It uses a six-layer board, 43 purchasable components and 216 connected pads.
Firmware runs the MCU at 96 MHz and the memory at 48 MHz, tests all 8 MiB,
and reports through status LEDs and a 3.3 V UART.

Manufacturing readiness is recorded in `output/readiness.json` and verified
against the exact source, rules, evidence and exported package. Use
`output/manufacturing.zip` only when that report is current and Ready.
Hardware testing remains pending; this design has not yet run on an assembled
board.

## Build and assembly

The reviewed physical source and build instructions are in
[`real_design/`](real_design/README.md). The electrical circuit is independently
regenerated and compared with the reviewed packages and every pad-to-net
binding. Routing is preserved as reviewed source and independently rechecked;
this is not a claim that an unconstrained autorouter produces identical copper.

The factory construction is JLC06161H-2116A, nominal 1.6 mm, with four signal
layers and dedicated ground/3.3 V reference planes. See the
[fabrication requirements](real_design/manufacturing-requirements.md).
The assembly BOM and placement file cover 40 SMT parts, including 25
back-side capacitors, and three through-hole headers. Check J1, J2, J3 and
U2 against the assembly drawings in JLCPCB’s placement preview. The
procurement list gives the manufacturer part numbers and supplier
references. [Procurement list](real_design/procurement.json)

Supply regulated 5 V ±5% at J1 pin 1 and ground at pin 2. Use an external SWD
probe at J2 and a 3.3 V UART adapter at J3. The initial bench envelope is
0–30 °C ambient and at most 230 mA continuous board current. Check the power
rails and regulator temperature during first bring-up. See the
[firmware/programming instructions](real_design/firmware/README.md).

## Electrical review

All SDRAM groups have a 5 mm length-spread budget and each signal must be
within 10 mm of SDCLK, including actual vertical travel through vias.
The validator checks 45–55 ohm geometry on every bus layer and distinct
external load budgets: 15 pF for SDCLK and 30 pF for the other drivers.
Clock track/via spacing is measured symmetrically on all signal layers.

Short front-side package escapes require an explicit engineering review of
the data/control separation recommendation. Their measured geometry and
model assumptions are documented in [the electrical review](real_design/engineering/README.md).
No IBIS corner qualification or bench validation is implied by a manufacturing
or model-based check.

## Synthetic regression witness

The previous nonfunctional fixture remains in
[`regression-fixture/`](regression-fixture/README.md) for Epic #2661 regression
coverage. Legacy `generate_design.py` defaults to `regression-output/` and
must not be used to generate this assembled demo. Its synthetic pinouts and
historical routing failures are not manufacturing artifacts.

The legacy recipe routes on the lattice engine
(`--route-engine lattice --strategy basic --differential-pairs`) since
issue #6448. Before that it used the default grid engine
(`--strategy negotiated`), the grid coupled pre-pass and the placement-delta
feedback loop. The loop is off now: it re-routes with the grid router, and the
lattice route already reaches 31/31. See
[`regression-fixture/README.md`](regression-fixture/README.md#ci-gate-phase-3n-2726)
for the measured numbers.

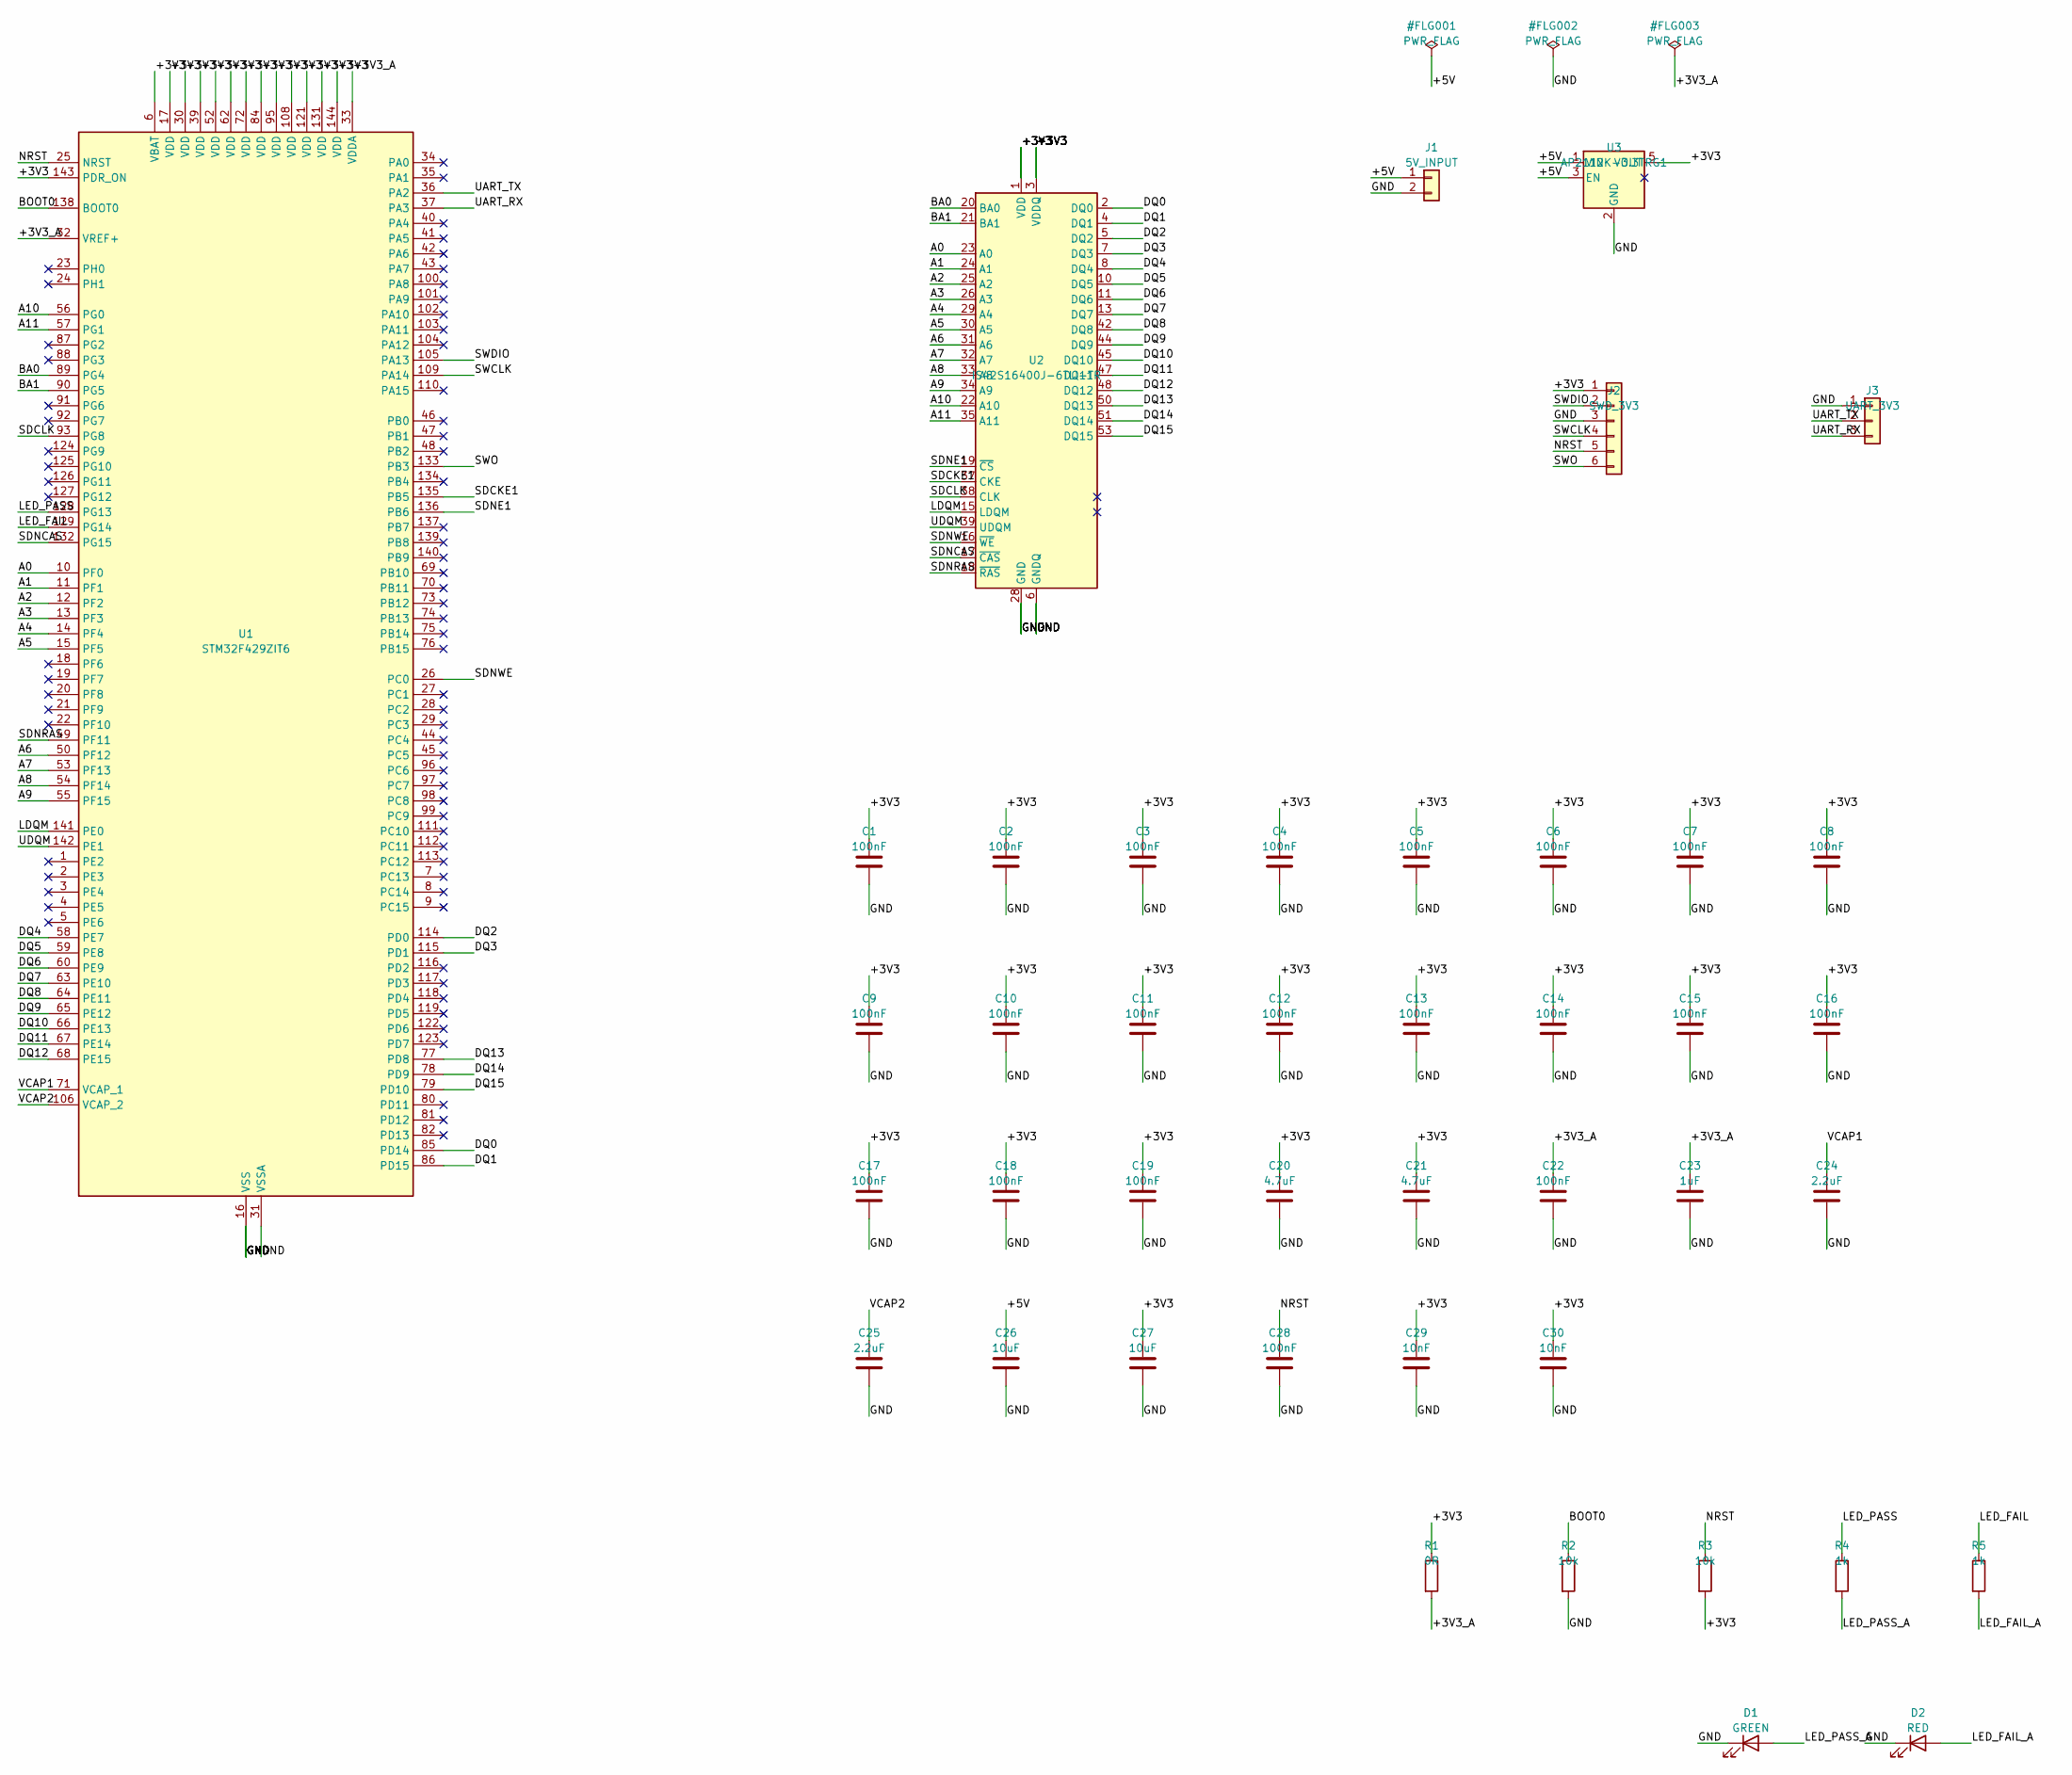
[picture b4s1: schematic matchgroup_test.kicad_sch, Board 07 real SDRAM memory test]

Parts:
C1, C2, C3, C4, C5, C6, C7, C8, C9, C10, C11, C12, C13, C14, C15, C16, C17, C18, C19, C22, C28: 100nF; C_0603_1608Metric; Manufacturer_Part_Number CC0603KRX7R9BB104; LCSC C14663
C20, C21: 4.7uF; C_0603_1608Metric; Manufacturer_Part_Number CL10A475KP8NNNC; LCSC C1705
C23: 1uF; C_0603_1608Metric; Manufacturer_Part_Number CL10A105KB8NNNC; LCSC C15849
C24, C25: 2.2uF; C_0603_1608Metric; Manufacturer_Part_Number CL10A225KO8NNNC; LCSC C23630
C26, C27: 10uF; C_0603_1608Metric; Manufacturer_Part_Number CL10A106KP8NNNC; LCSC C19702
C29, C30: 10nF; C_0603_1608Metric; Manufacturer_Part_Number CL10B103KB8NNNC; LCSC C1589
D1: GREEN; LED_0603_1608Metric; Manufacturer_Part_Number LTST-C190KGKT; LCSC C125094
D2: RED; LED_0603_1608Metric; Manufacturer_Part_Number LTST-C190KRKT; LCSC C94869
J1: 5V_INPUT; PinHeader_1x02_P2.54mm_Vertical; Manufacturer_Part_Number B-2100S02P-A110; LCSC C124375
J2: SWD_3V3; PinHeader_1x06_P2.54mm_Vertical; Manufacturer_Part_Number 2.54-1x6P; LCSC C37208
J3: UART_3V3; PinHeader_1x03_P2.54mm_Vertical; Manufacturer_Part_Number 2.54-1*3P; LCSC C49257
R1: 0R; R_0603_1608Metric; Manufacturer_Part_Number 0603WAF0000T5E; LCSC C21189
R2, R3: 10k; R_0603_1608Metric; Manufacturer_Part_Number 0603WAF1002T5E; LCSC C25804
R4, R5: 1k; R_0603_1608Metric; Manufacturer_Part_Number 0603WAF1001T5E; LCSC C21190
U1: STM32F429ZIT6; LQFP-144_20x20mm_P0.5mm; Manufacturer_Part_Number STM32F429ZIT6; LCSC C84808
U2: IS42S16400J-6TLI-TR; TSOP-II-54_22.2x10.16mm_P0.8mm; Manufacturer_Part_Number IS42S16400J-6TLI-TR; LCSC C17216754
U3: AP2112K-3.3TRG1; SOT-23-5; Manufacturer_Part_Number AP2112K-3.3TRG1; LCSC C51118

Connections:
+3V3: C1.1, C2.1, C3.1, C4.1, C5.1, C6.1, C7.1, C8.1, C9.1, C10.1, C11.1, C12.1, C13.1, C14.1, C15.1, C16.1, C17.1, C18.1, C19.1, C20.1, C21.1, C27.1, C29.1, C30.1, J2.1, R1.1, R3.2, U1.6 (VBAT), U1.17 (VDD), U1.30 (VDD), U1.39 (VDD), U1.52 (VDD), U1.62 (VDD), U1.72 (VDD), U1.84 (VDD), U1.95 (VDD), U1.108 (VDD), U1.121 (VDD), U1.131 (VDD), U1.143 (PDR_ON), U1.144 (VDD), U2.1 (VDD), U2.3 (VDDQ), U2.9 (VDDQ), U2.14 (VDD), U2.27 (VDD), U2.43 (VDDQ), U2.49 (VDDQ), U3.5 (VOUT)
+3V3_A: C22.1, C23.1, R1.2, U1.32 (VREF+), U1.33 (VDDA)
+5V: C26.1, J1.1, U3.1 (VIN), U3.3 (EN)
A0: U1.10 (PF0), U2.23 (A0)
A1: U1.11 (PF1), U2.24 (A1)
A2: U1.12 (PF2), U2.25 (A2)
A3: U1.13 (PF3), U2.26 (A3)
A4: U1.14 (PF4), U2.29 (A4)
A5: U1.15 (PF5), U2.30 (A5)
A6: U1.50 (PF12), U2.31 (A6)
A7: U1.53 (PF13), U2.32 (A7)
A8: U1.54 (PF14), U2.33 (A8)
A9: U1.55 (PF15), U2.34 (A9)
A10: U1.56 (PG0), U2.22 (A10)
A11: U1.57 (PG1), U2.35 (A11)
BA0: U1.89 (PG4), U2.20 (BA0)
BA1: U1.90 (PG5), U2.21 (BA1)
BOOT0: R2.1, U1.138 (BOOT0)
DQ0: U1.85 (PD14), U2.2 (DQ0)
DQ1: U1.86 (PD15), U2.4 (DQ1)
DQ2: U1.114 (PD0), U2.5 (DQ2)
DQ3: U1.115 (PD1), U2.7 (DQ3)
DQ4: U1.58 (PE7), U2.8 (DQ4)
DQ5: U1.59 (PE8), U2.10 (DQ5)
DQ6: U1.60 (PE9), U2.11 (DQ6)
DQ7: U1.63 (PE10), U2.13 (DQ7)
DQ8: U1.64 (PE11), U2.42 (DQ8)
DQ9: U1.65 (PE12), U2.44 (DQ9)
DQ10: U1.66 (PE13), U2.45 (DQ10)
DQ11: U1.67 (PE14), U2.47 (DQ11)
DQ12: U1.68 (PE15), U2.48 (DQ12)
DQ13: U1.77 (PD8), U2.50 (DQ13)
DQ14: U1.78 (PD9), U2.51 (DQ14)
DQ15: U1.79 (PD10), U2.53 (DQ15)
GND: C1.2, C2.2, C3.2, C4.2, C5.2, C6.2, C7.2, C8.2, C9.2, C10.2, C11.2, C12.2, C13.2, C14.2, C15.2, C16.2, C17.2, C18.2, C19.2, C20.2, C21.2, C22.2, C23.2, C24.2, C25.2, C26.2, C27.2, C28.2, C29.2, C30.2, D1.1 (K), D2.1 (K), J1.2, J2.3, J3.1, R2.2, U1.16 (VSS), U1.31 (VSSA), U1.38 (VSS), U1.51 (VSS), U1.61 (VSS), U1.83 (VSS), U1.94 (VSS), U1.107 (VSS), U1.120 (VSS), U1.130 (VSS), U2.6 (GNDQ), U2.12 (GNDQ), U2.28 (GND), U2.41 (GND), U2.46 (GNDQ), U2.52 (GNDQ), U2.54 (GND), U3.2 (GND)
LDQM: U1.141 (PE0), U2.15 (LDQM)
LED_FAIL: R5.1, U1.129 (PG14)
LED_FAIL_A: D2.2 (A), R5.2
LED_PASS: R4.1, U1.128 (PG13)
LED_PASS_A: D1.2 (A), R4.2
NRST: C28.1, J2.5, R3.1, U1.25 (NRST)
SDCKE1: U1.135 (PB5), U2.37 (CKE)
SDCLK: U1.93 (PG8), U2.38 (CLK)
SDNCAS: U1.132 (PG15), U2.17 (~CAS)
SDNE1: U1.136 (PB6), U2.19 (~CS)
SDNRAS: U1.49 (PF11), U2.18 (~RAS)
SDNWE: U1.26 (PC0), U2.16 (~WE)
SWCLK: J2.4, U1.109 (PA14)
SWDIO: J2.2, U1.105 (PA13)
SWO: J2.6, U1.133 (PB3)
UART_RX: J3.3, U1.37 (PA3)
UART_TX: J3.2, U1.36 (PA2)
UDQM: U1.142 (PE1), U2.39 (UDQM)
VCAP1: C24.1, U1.71 (VCAP_1)
VCAP2: C25.1, U1.106 (VCAP_2)

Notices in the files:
README.md:
License:
MIT
License: MIT
load-bearing: an AGPL or unlicensed neighbour is studied at the capability
- **[TraceMaker](https://github.com/DingoOz/TraceMaker)** (GPL-3.0-or-later, C++20 + CUDA, 42★) -- **Benchmarked against us.** C++20/CUDA KiCad 9/10 router that reads and writes `.kicad_pcb` directly and is judged by `kicad-cli` DRC.
- **[freerouting](https://github.com/freerouting/freerouting)** (GPL-3.0, Java, 2068★) -- the long-standing Specctra DSN/SES autorouter and the baseline most KiCad users try first.
No LICENSE: all rights reserved, ideas only.
